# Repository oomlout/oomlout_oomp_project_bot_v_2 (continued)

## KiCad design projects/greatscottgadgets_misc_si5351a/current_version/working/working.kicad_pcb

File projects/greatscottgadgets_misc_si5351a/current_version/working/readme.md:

# misc
 
## summary 
* id: greatscottgadgets_misc_si5351a
* user: greatscottgadgets
* name: misc
* board: si5351a
* repo: https://github.com/greatscottgadgets/misc
* src_file_repo_kicad_pcb: evaluation-boards/Si5351A/Si5351A.kicad_pcb
* src_file_repo_kicad_pcb_link: https://github.com/greatscottgadgets/misc/tree/master/evaluation-boards/Si5351A/Si5351A.kicad_pcb
* src_file_repo_kicad_sch: evaluation-boards/Si5351A/Si5351A.kicad_sch
* src_file_repo_kicad_sch_link: https://github.com/greatscottgadgets/misc/tree/master/evaluation-boards/Si5351A/Si5351A.kicad_sch

* src_file_repo_sch: evaluation-boards/quad-balun-directional-coupler/quad-balun-directional-coupler.sch
* src_file_repo_sch_link: https://github.com/greatscottgadgets/misc/tree/master/evaluation-boards/quad-balun-directional-coupler/quad-balun-directional-coupler.sch
* full details link: https://github.com/oomlout/oomlout_oomp_project_bot_v_2/tree/main/projects/greatscottgadgets_misc_si5351a/current_version/working

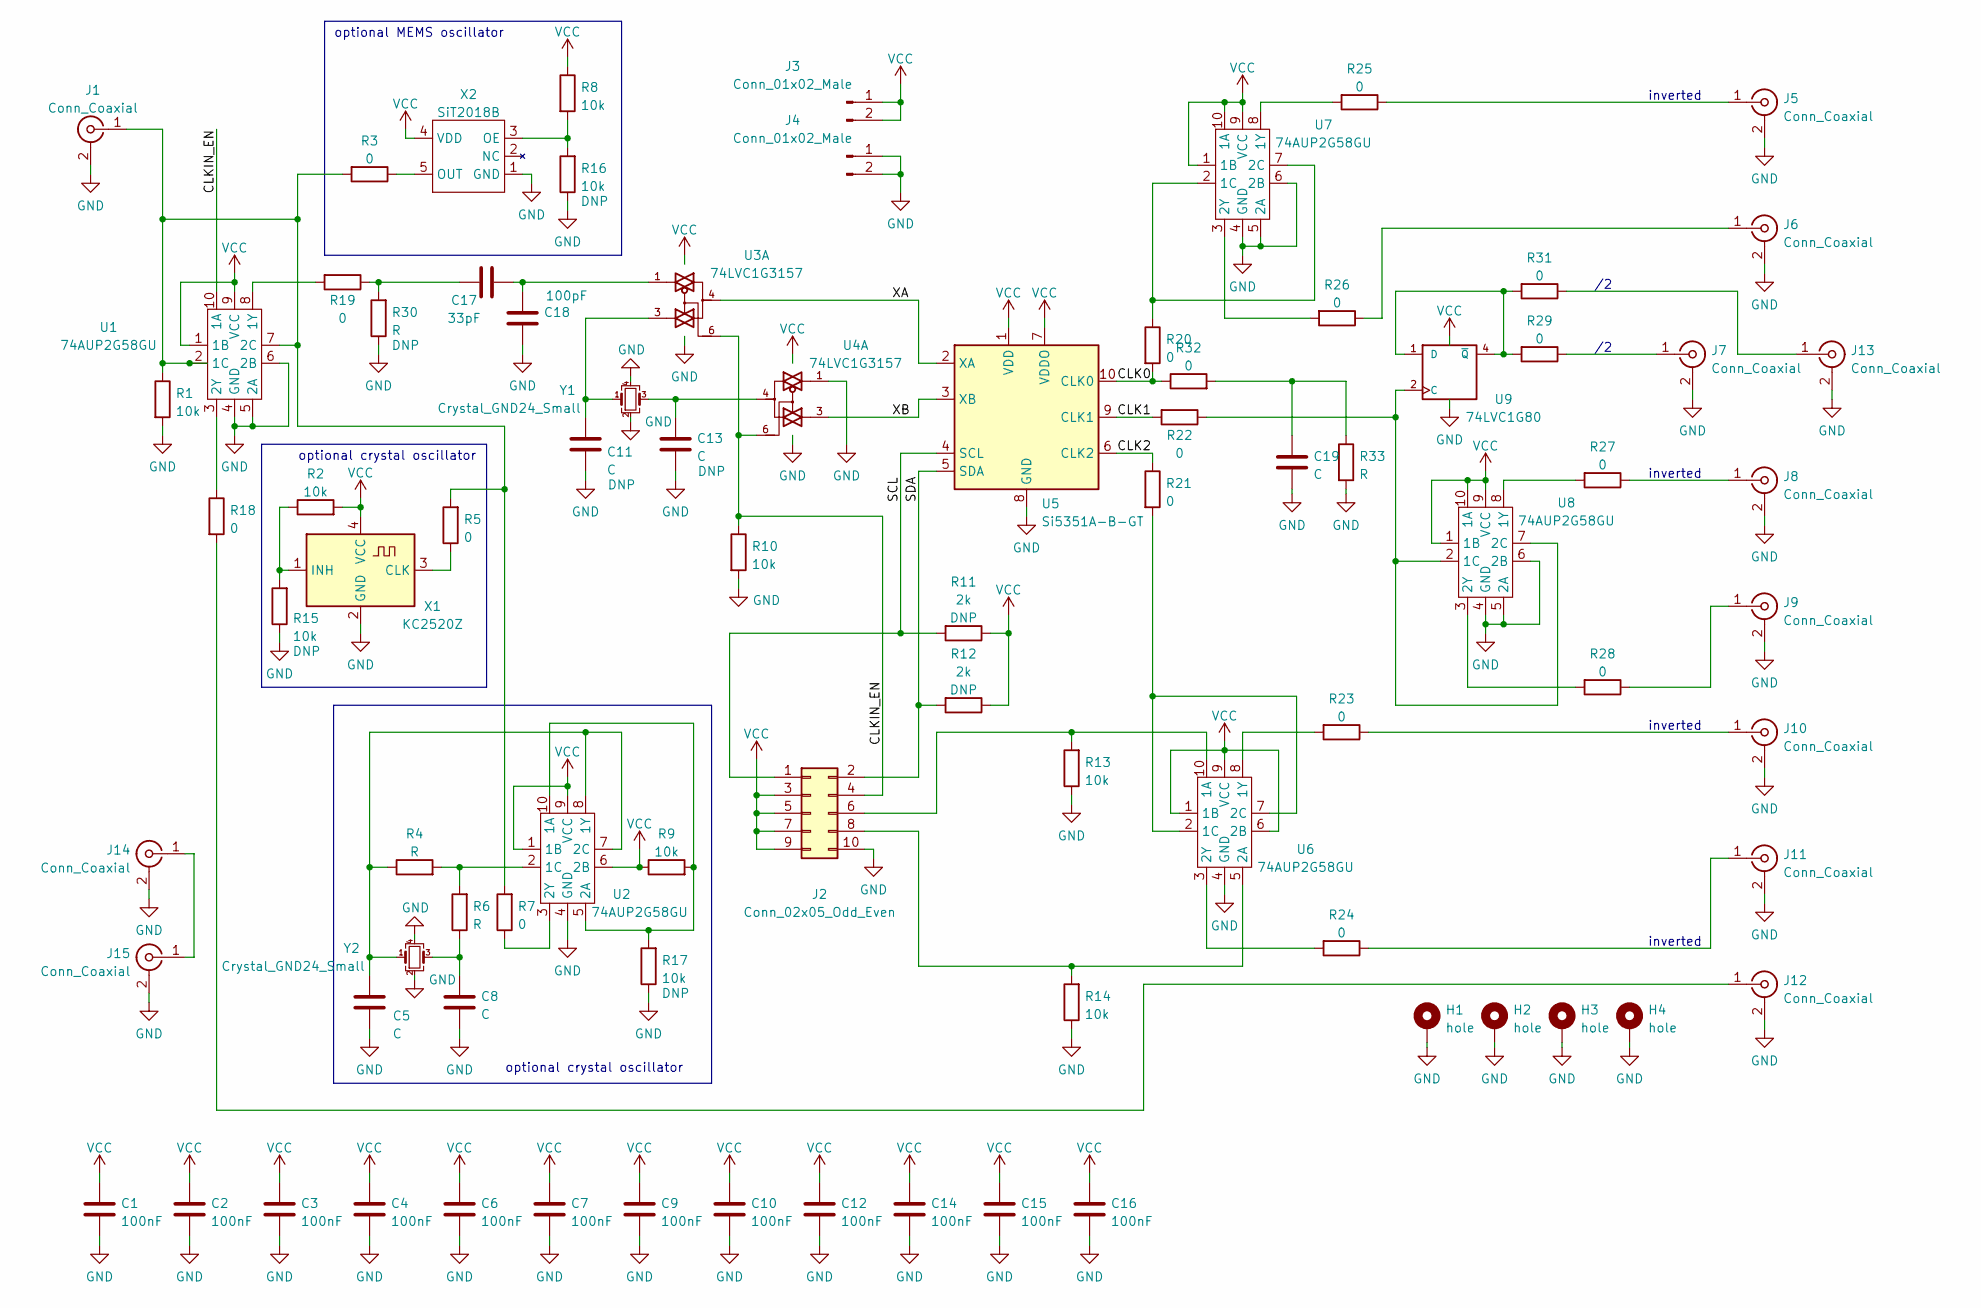
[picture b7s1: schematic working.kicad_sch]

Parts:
C1, C2, C3, C4, C6, C7, C9, C10, C12, C14, C15, C16: 100nF; C_0402_1005Metric
C5, C8, C11, C13, C19: C; C_0402_1005Metric
C17: 33pF; C_0402_1005Metric
C18: 100pF; C_0402_1005Metric
H1, H2, H3, H4: hole; MountingHole_2.2mm_M2_Pad_Via
J1, J5, J6, J7, J8, J9, J10, J11, J12, J13, J14, J15: Conn_Coaxial; SMA-EDGE
J2: Conn_02x05_Odd_Even; PinHeader_2x05_P2.54mm_Vertical
J3, J4: Conn_01x02_Male; PinHeader_1x02_P2.54mm_Vertical
R1, R2, R8, R9, R10, R13, R14, R15, R16, R17: 10k; R_0402_1005Metric
R3, R5, R7, R18, R19, R20, R21, R22, R23, R24, R25, R26, R27, R28, R29, R31, R32: 0; R_0402_1005Metric
R4, R6, R30, R33: R; R_0402_1005Metric
R11, R12: 2k; R_0402_1005Metric
U1, U2, U6, U7, U8: 74AUP2G58GU; XQFN10; Part Number 74AUP2G58GUX
U3, U4: 74LVC1G3157; XSON6; Part Number 74LVC1G3157GM,115
U5: Si5351A-B-GT; MSOP-10_3x3mm_P0.5mm; Part Number Si5351A-B-GTR
U9: 74LVC1G80; SOT-353_SC-70-5; Part Number SN74LVC1G80DCKR
X1: KC2520Z; Oscillator_SMD_Kyocera_KC2520Z-4Pin_2.5x2.0mm; Part Number KC2520Z25.0000C1KX00
X2: SiT2018B; SOT-23-5; Part Number SIT2018BEAS1-33N-27.000000E
Y1, Y2: Crystal_GND24_Small; Crystal_SMD_3225-4Pin_3.2x2.5mm

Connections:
/CLK0: R20.2, R32.1, U5.10 (CLK0)
/CLK1: R22.2, U5.9 (CLK1)
/CLK2: R21.1, U5.6 (CLK2)
/CLKIN_EN: J2.4, R10.1, U1.10 (1A), U3.6, U4.6
/SCL: J2.1, R11.2, U5.4 (SCL)
/SDA: J2.2, R12.2, U5.5 (SDA)
/XA: U3.4, U5.2 (XA)
/XB: U4.3, U5.3 (XB)
GND: C1.2, C2.2, C3.2, C4.2, C5.2, C6.2, C7.2, C8.2, C9.2, C10.2, C11.2, C12.2, C13.2, C14.2, C15.2, C16.2, C18.2, C19.2, H1.1, H2.1, H3.1, H4.1, J1.2 (Ext), J2.10, J4.1, J4.2, J5.2 (Ext), J6.2 (Ext), J7.2 (Ext), J8.2 (Ext), J9.2 (Ext), J10.2 (Ext), J11.2 (Ext), J12.2 (Ext), J13.2 (Ext), J14.2 (Ext), J15.2 (Ext), R1.2, R10.2, R13.1, R14.1, R15.1, R16.1, R17.1, R30.1, R33.2, U1.4 (GND), U1.5 (2A), U1.6 (2B), U2.4 (GND), U3.2 (GND), U4.1, U4.2 (GND), U5.8 (GND), U6.4 (GND), U7.4 (GND), U7.5 (2A), U7.6 (2B), U8.4 (GND), U8.5 (2A), U8.6 (2B), U9.3 (GND), X1.2 (GND), X2.1 (GND), Y1.2, Y1.4, Y2.2, Y2.4
unnamed: C5.1, R4.1, U2.7 (2C), U2.8 (1Y), Y2.1
unnamed: C8.1, R6.1, Y2.3
unnamed: C11.1, U3.3, Y1.1
unnamed: C13.1, U4.4, Y1.3
unnamed: C17.1, R19.1, R30.2
unnamed: C17.2, C18.1, U3.1
unnamed: C19.1, R32.2, R33.1
unnamed: J1.1 (In), R1.1, R3.2, R5.2, R7.2, U1.2 (1C), U1.7 (2C)
unnamed: J2.6, R13.2, U6.10 (1A)
unnamed: J2.8, R14.2, U6.5 (2A)
unnamed: J5.1 (In), R25.1
unnamed: J6.1 (In), R26.1
unnamed: J7.1 (In), R29.1
unnamed: J8.1 (In), R27.1
unnamed: J9.1 (In), R28.1
unnamed: J10.1 (In), R23.1
unnamed: J11.1 (In), R24.1
unnamed: J12.1 (In), R18.2
unnamed: J13.1 (In), R31.1
unnamed: J14.1 (In), J15.1 (In)
unnamed: R3.1, X2.5 (OUT)
unnamed: R4.2, R6.2, U2.2 (1C)
unnamed: R5.1, X1.3 (CLK)
unnamed: R7.1, U2.3 (2Y)
unnamed: R2.1, R15.2, X1.1 (INH)
unnamed: R8.2, R16.2, X2.3 (OE)
unnamed: R9.2, R17.2, U2.5 (2A), U2.10 (1A)
unnamed: R18.1, U1.3 (2Y)
unnamed: R19.2, U1.8 (1Y)
unnamed: R20.1, U7.2 (1C), U7.7 (2C)
unnamed: R21.2, U6.2 (1C), U6.7 (2C)
unnamed: R22.1, U8.2 (1C), U8.7 (2C), U9.2 (C)
unnamed: R23.2, U6.8 (1Y)
unnamed: R24.2, U6.3 (2Y)
unnamed: R25.2, U7.8 (1Y)
unnamed: R26.2, U7.3 (2Y)
unnamed: R27.2, U8.8 (1Y)
unnamed: R28.2, U8.3 (2Y)
unnamed: R29.2, R31.2, U9.1 (D), U9.4 (~Q)
VCC: C1.1, C2.1, C3.1, C4.1, C6.1, C7.1, C9.1, C10.1, C12.1, C14.1, C15.1, C16.1, J2.3, J2.5, J2.7, J2.9, J3.1, J3.2, R2.2, R8.1, R9.1, R11.1, R12.1, U1.1 (1B), U1.9 (VCC), U2.1 (1B), U2.6 (2B), U2.9 (VCC), U3.5 (VCC), U4.5 (VCC), U5.1 (VDD), U5.7 (VDDO), U6.1 (1B), U6.6 (2B), U6.9 (VCC), U7.1 (1B), U7.9 (VCC), U7.10 (1A), U8.1 (1B), U8.9 (VCC), U8.10 (1A), U9.5 (VCC), X1.4 (VCC), X2.4 (VDD)

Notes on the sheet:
inverted
optional MEMS oscillator
optional crystal oscillator

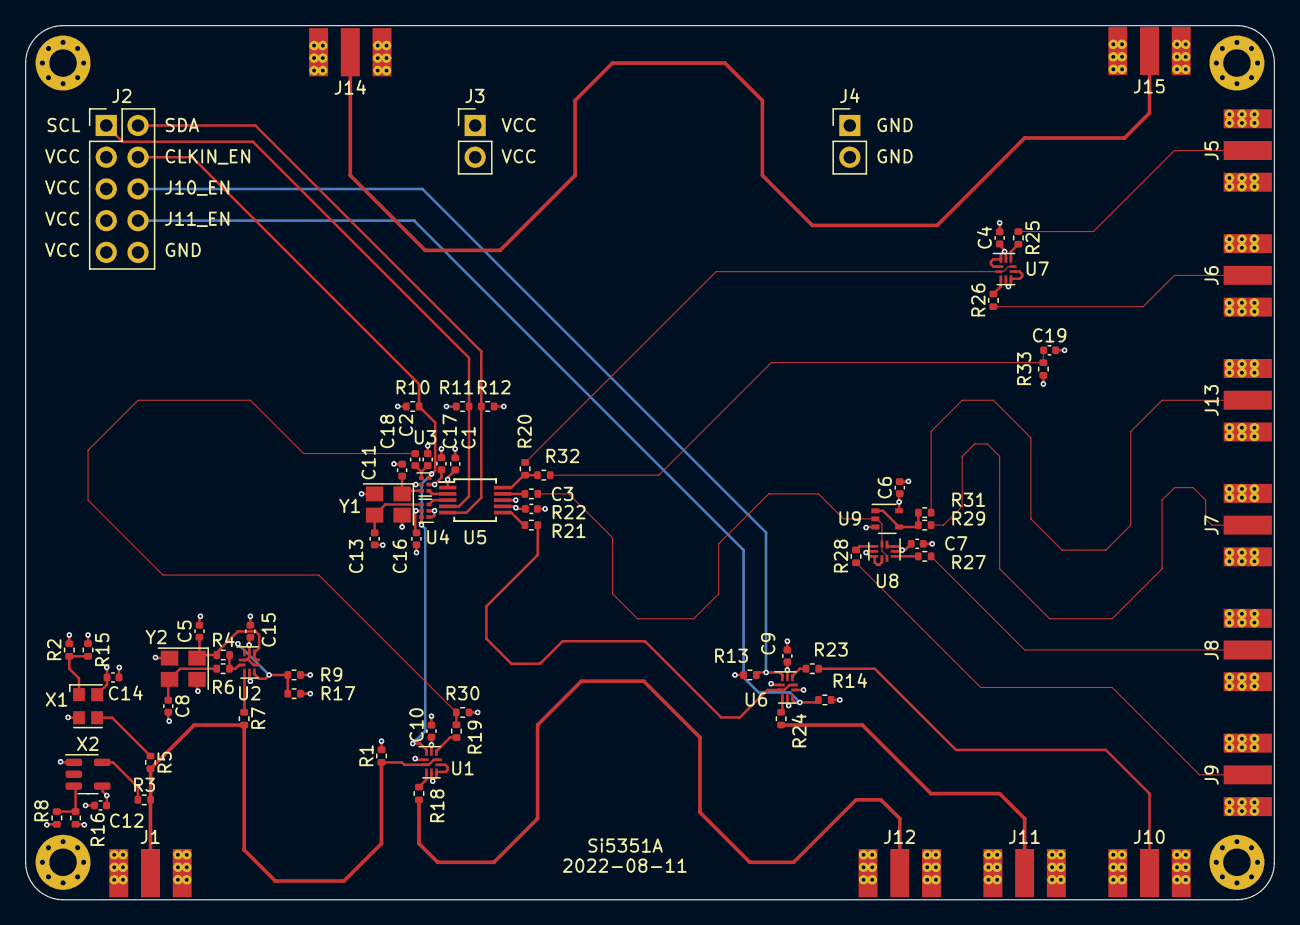
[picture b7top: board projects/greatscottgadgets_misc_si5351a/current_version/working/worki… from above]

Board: 4 copper layers, 100.0 x 70.0 mm, 84 parts (0 on the bottom side), 49 nets.

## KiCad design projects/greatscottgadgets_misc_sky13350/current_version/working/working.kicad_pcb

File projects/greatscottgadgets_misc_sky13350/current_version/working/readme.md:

# misc
 
## summary 
* id: greatscottgadgets_misc_sky13350
* user: greatscottgadgets
* name: misc
* board: sky13350
* repo: https://github.com/greatscottgadgets/misc
* src_file_repo_kicad_pcb: evaluation-boards/sky13350/sky13350.kicad_pcb
* src_file_repo_kicad_pcb_link: https://github.com/greatscottgadgets/misc/tree/master/evaluation-boards/sky13350/sky13350.kicad_pcb
* src_file_repo_kicad_sch: evaluation-boards/Si5351A/Si5351A.kicad_sch
* src_file_repo_kicad_sch_link: https://github.com/greatscottgadgets/misc/tree/master/evaluation-boards/Si5351A/Si5351A.kicad_sch

* src_file_repo_sch: evaluation-boards/sky13350/sky13350.sch
* src_file_repo_sch_link: https://github.com/greatscottgadgets/misc/tree/master/evaluation-boards/sky13350/sky13350.sch
* full details link: https://github.com/oomlout/oomlout_oomp_project_bot_v_2/tree/main/projects/greatscottgadgets_misc_sky13350/current_version/working

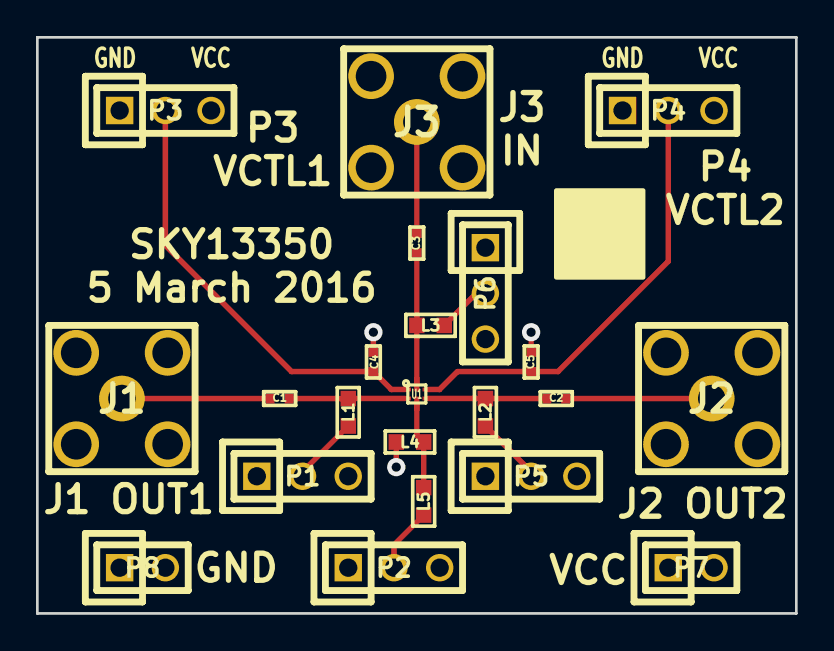
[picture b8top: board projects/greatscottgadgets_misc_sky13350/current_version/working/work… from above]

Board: 4 copper layers, 42.2 x 32.0 mm, 22 parts (0 on the bottom side), 15 nets.

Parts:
C1, C2, C3: 100nF; 0402
C4, C5: 33pF; 0402
J1, J2, J3: SMA; SMA-VERTICAL
L1, L2, L3, L4, L5: 15uH; 0603
P1, P2, P3, P4, P5, P6: CONN_01X03; HEADER-1x3
P7, P8: CONN_01X02; HEADER-1x2
U1: SKY13350; SKY13350-385LF

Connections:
GND: C4.2, C5.1, J1.2, J2.2, J3.2, L4.1, P1.1, P2.1, P3.1, P4.1, P5.1, P6.1, P8.1, P8.2
unnamed: C1.1, L1.2, U1.2
unnamed: C1.2, J1.1
unnamed: C2.1, J2.1
unnamed: C2.2, L2.2, U1.4
unnamed: C3.1, J3.1
unnamed: C3.2, L3.2, U1.6
unnamed: C4.1, P3.2, U1.1
unnamed: C5.2, P4.2, U1.5
unnamed: L1.1, P1.2
unnamed: L2.1, P5.2
unnamed: L3.1, P6.2
unnamed: L4.2, L5.2, U1.3
unnamed: L5.1, P2.2
VCC: P1.3, P2.3, P3.3, P4.3, P5.3, P6.3, P7.1, P7.2
